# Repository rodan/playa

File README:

This project has the following feature set:

   - a smallish and spartan music player that can work for weeks between charges
   - a 2Ah Li-poly cell and an integrated charger - 5V input
   - decoding of ogg vorbis, mp3 files
   - microSD (SDHC) is the storage medium. so fat32 and cards bigger than 4G.

  there are 2 components in this repository:
  avr        - contains the C source code for an Atmel-based microcontroller
  beaglebone - contains the C source code for beagle-bone (ARMv7)-based tools
  hardware   - open source hardware for the main board
				the schematic is based on VLSI's Simple DSP Evaluation Board [1]

  Library dependencies for the avr code:

   if using the master branch:
      none (this is a fully standalone version)

   if using the old 'arduino' branch:
      sdfatlib    http://code.google.com/p/sdfatlib/
      vs1063      https://github.com/rodan/vs1063
      IRremote    https://github.com/shirriff/Arduino-IRremote

  Usage:
   - an RC5 remote control provides the control (a Vishay TSOP IR receiver's output goes to PD2).
   - by default music files are played randomly. the following buttons are configured:
   
    VOL-        decrease volume
    VOL+        increase volume
    SUBTITLES   switch between 4 levels of spatial processing (for headphones)
    REWIND      switch to album mode
    CHANNEL-    switch to artist mode
    CHANNEL+    next track in either of the modes
    STOP        sends the player in low power shutdown mode. 
                you need to start it again to exit this.
    NUMBERS 0-9 select artist (which directory from the root of the filesystem to play)
    AV          disable artist selection

  Power consumption profile:
   - jumper/switch open - battery connected only to the charging circuit - < 3uA
   - normal file decoding - 30-40 mA
   - shutdown (after STOP ir command), IR sensor active - 800uA
   - after uC woken up by ir sensor trigger, waiting for a POWER ir sequence (for max 2 seconds) - 4.5mA (this mode has been disabled in the code)
   - if the stereo jack is unused or if the battery level goes below safe LiPo levels then the player enters shutdown mode.

  Known problems and limitations:
   - you should format the SDcard as Fat32 with largest available cluster size
   - no special chars must be used in the filesystem entries, only ascii alphanumeric chars
   - there is a hardcoded MAX_PATH that only allows about 4 parent dirs to any music file

  Tested with:
   - 16G Class 10 Adata card, with ogg files over the 4G barrier

  Author:            Petre Rodan <2b4eda@subdimension.ro>
  Available from:    https://github.com/rodan/playa
  Product pictures:  https://photos.app.goo.gl/nUQuD7HJvfVBpMeQ9
  License:           GNU GPLv3

[1]  http://www.vlsi.fi/en/support/evaluationboards/vs1053vs8053simpledspboard.html

 GNU GPLv3 license:
  
  This program is free software: you can redistribute it and/or modify
  it under the terms of the GNU General Public License as published by
  the Free Software Foundation, either version 3 of the License, or
  (at your option) any later version.
   
  This program is distributed in the hope that it will be useful,
  but WITHOUT ANY WARRANTY; without even the implied warranty of
  MERCHANTABILITY or FITNESS FOR A PARTICULAR PURPOSE.  See the
  GNU General Public License for more details.
   
  You should have received a copy of the GNU General Public License
  along with this program.  If not, see <http://www.gnu.org/licenses/>.

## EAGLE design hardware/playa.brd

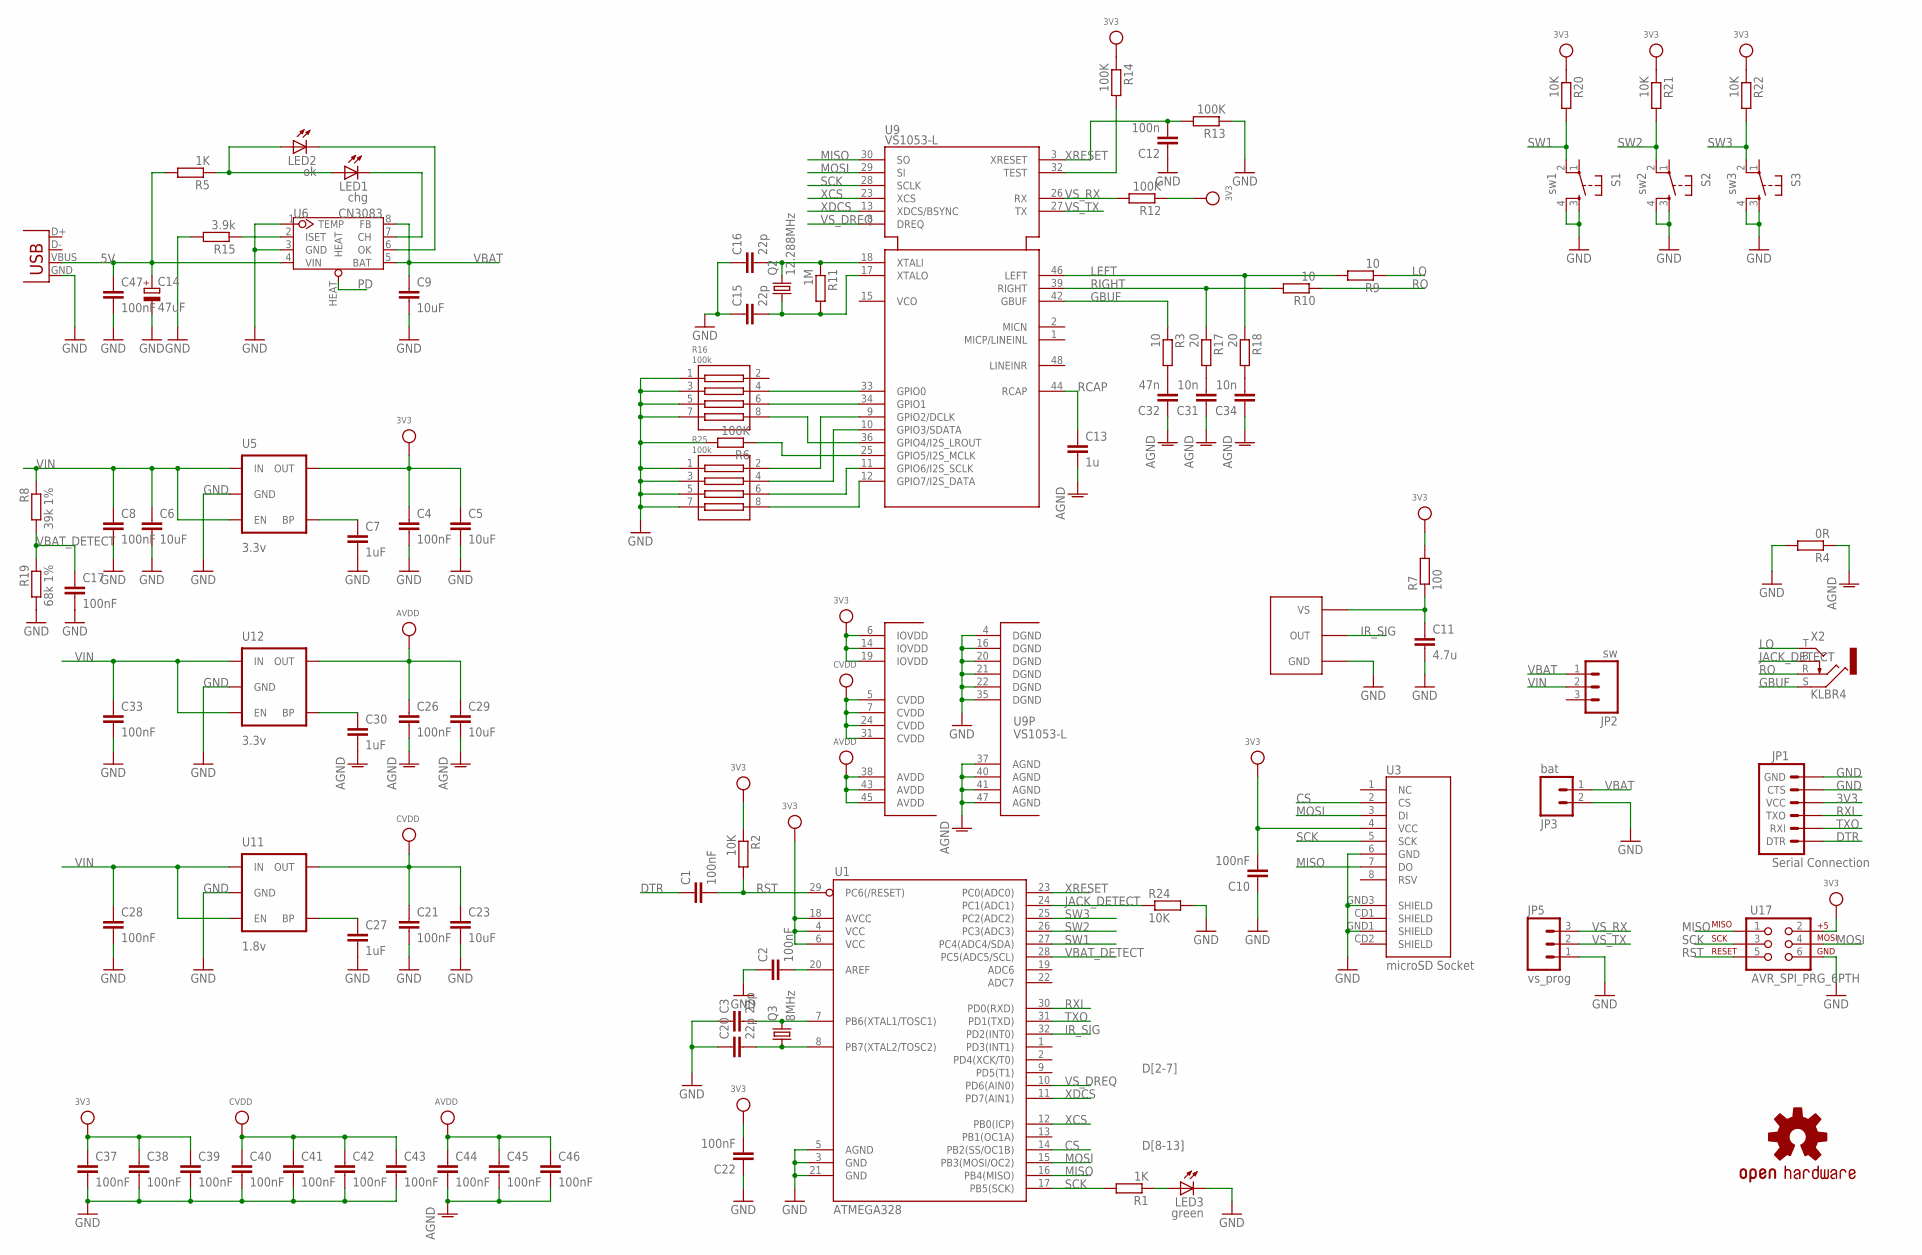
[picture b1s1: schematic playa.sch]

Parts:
C1, C2, C4, C8, C10, C17, C21, C22, C26, C28, C33, C37, C38, C39, C40, C41, C42, C43, C44, C45, C46, C47: 100nF; C0805
C3, C15, C16, C20: 22p; C0805
C5, C6, C9, C23, C29: 10uF; C1206
C7, C27, C30: 1uF; C0805
C11: 4.7u; C1206
C12: 100n; C0805
C13: 1u; C0805
C14: 47uF; CT7343
C31, C34: 10n; C0805
C32: 47n; C0805
JP1: Serial Connection; 1X06
JP2: sw; 1X03
JP3: bat; 1X02
JP5: vs_prog; 1X03
LED1: chg; CHIP-LED0805
LED2: ok; CHIP-LED0805
LED3: green; CHIP-LED0805
Q2: 12.288MHz; CRYSTAL_5X3.2
Q3: 8MHz; CRYSTAL_5X3.2
R1, R5: 1K; R0805W
R2, R20, R21, R22, R24: 10K; R0805W
R3, R9, R10: 10; R0805W
R4: 0R; R0805W
R6, R12, R13, R14: 100K; R0805W
R7: 100; R0805W
R8: 39k 1%; R0805W
R11: 1M; R0805W
R15: 3.9k; R0805W
R16, R25: 100k; RAS_ARR_1206
R17, R18: 20; R0805W
R19: 68k 1%; R0805W
S1: sw1; TACTILE_SWITCH_SMD
S2: sw2; TACTILE_SWITCH_SMD
S3: sw3; TACTILE_SWITCH_SMD
U1: ATMEGA328; TQFP32-08
U3: microSD Socket; MICRO-SD-SOCKET-PP
U5, U12: 3.3v; SOT23-5
U6: CN3083; SOP8-W/-HEAT
U9: VS1053-L; LQFP48
U11: 1.8v; SOT23-5
U17: AVR_SPI_PRG_6PTH; 2X3
U$3: TSOP312X
U$5: OSHW-LOGOM; OSHW-LOGO-M
X1: USBSMD; USB-MINIB
X2: KLBR4

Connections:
3V3: C4.1, C5.1, C10.2, C22.2, C37.1, C38.1, C39.1, JP1.4 (VCC), R2.1, R7.2, R12.1, R14.1, R20.1, R21.1, R22.1, U1.4 (VCC), U1.6 (VCC), U1.18 (AVCC), U3.4 (VCC), U5.5 (OUT), U9.6 (IOVDD), U9.14 (IOVDD), U9.19 (IOVDD), U17.2
5V: C14.+, C47.1, R5.2, U6.4 (VIN), X1.VBUS
AGND: C13.2, C26.2, C29.2, C30.2, C31.1, C32.1, C34.1, C44.2, C45.2, C46.2, R4.1, U9.37 (AGND), U9.40 (AGND), U9.41 (AGND), U9.47 (AGND)
AVDD: C26.1, C29.1, C44.1, C45.1, C46.1, U9.38 (AVDD), U9.43 (AVDD), U9.45 (AVDD), U12.5 (OUT)
CS: U1.14 (PB2(SS/OC1B)), U3.2 (CS)
CVDD: C21.1, C23.1, C40.1, C41.1, C42.1, C43.1, U9.5 (CVDD), U9.7 (CVDD), U9.24 (CVDD), U9.31 (CVDD), U11.5 (OUT)
DTR: C1.1, JP1.1 (DTR)
GBUF: R3.1, U9.42 (GBUF), X2.S
GND: C2.1, C3.1, C4.2, C5.2, C6.2, C7.2, C8.2, C9.2, C10.1, C11.2, C12.1, C14.-, C15.1, C16.1, C17.2, C20.1, C21.2, C22.1, C23.2, C27.2, C28.2, C33.2, C37.2, C38.2, C39.2, C40.2, C41.2, C42.2, C43.2, C47.2, JP1.5 (CTS), JP1.6 (GND), JP3.2, JP5.1, LED3.C, R4.2, R6.2, R13.1, R15.2, R16.1, R16.3, R16.5, R16.7, R19.2, R24.2, R25.1, R25.3, R25.5, R25.7, S1.3, S1.4, S2.3, S2.4, S3.3, S3.4, U1.3 (GND), U1.5 (AGND), U1.21 (GND), U3.6 (GND), U3.GND1 (SHIELD), U3.GND3 (SHIELD), U5.2 (GND), U6.1 (TEMP), U6.3 (GND), U9.4 (DGND), U9.16 (DGND), U9.20 (DGND), U9.21 (DGND), U9.22 (DGND), U9.35 (DGND), U11.2 (GND), U12.2 (GND), U17.6, U$3.1 (GND), X1.GND
IR_SIG: U1.32 (PD2(INT0)), U$3.3 (OUT)
JACK_DETECT: R24.1, U1.24 (PC1(ADC1)), X2.B
LEFT: R9.2, R18.1, U9.46 (LEFT)
LO: R9.1, X2.T
MISO: U1.16 (PB4(MISO)), U3.7 (DO), U9.30 (SO), U17.1
MOSI: U1.15 (PB3(MOSI/OC2)), U3.3 (DI), U9.29 (SI), U17.4
unnamed: C20.2, Q3.P$1 (1), U1.8 (PB7(XTAL2/TOSC2))
unnamed: C3.2, Q3.P$2 (2), U1.7 (PB6(XTAL1/TOSC1))
unnamed: C2.2, U1.20 (AREF)
unnamed: R16.4, U9.33 (GPIO0)
unnamed: C7.1, U5.4 (BP)
unnamed: R25.8, U9.12 (GPIO7/I2S_DATA)
unnamed: C27.1, U11.4 (BP)
unnamed: C32.2, R3.2
unnamed: R15.1, U6.2 (ISET)
unnamed: C31.2, R17.2
unnamed: C34.2, R18.2
unnamed: R16.6, U9.34 (GPIO1)
unnamed: LED3.A, R1.1
unnamed: LED1.A, LED2.A, R5.1
unnamed: LED1.C, U6.7 (CH)
unnamed: LED2.C, U6.6 (OK)
unnamed: R16.8, U9.36 (GPIO4/I2S_LROUT)
unnamed: C30.1, U12.4 (BP)
unnamed: R6.1, U9.25 (GPIO5/I2S_MCLK)
unnamed: R25.2, U9.9 (GPIO2/DCLK)
unnamed: R25.4, U9.10 (GPIO3/SDATA)
unnamed: R25.6, U9.11 (GPIO6/I2S_SCLK)
unnamed: C11.1, R7.1, U$3.2 (VS)
unnamed: R14.2, U9.32 (TEST)
PD: U6.HEAT
RCAP: C13.1, U9.44 (RCAP)
RIGHT: R10.2, R17.1, U9.39 (RIGHT)
RO: R10.1, X2.R
RST: C1.2, R2.2, U1.29 (PC6(/RESET)), U17.5
RXI: JP1.3 (TXO), U1.30 (PD0(RXD))
SCK: R1.2, U1.17 (PB5(SCK)), U3.5 (SCK), U9.28 (SCLK), U17.3
SW1: R20.2, S1.2, U1.27 (PC4(ADC4/SDA))
SW2: R21.2, S2.2, U1.26 (PC3(ADC3))
SW3: R22.2, S3.2, U1.25 (PC2(ADC2))
TXO: JP1.2 (RXI), U1.31 (PD1(TXD))
VBAT: C9.1, JP2.1, JP3.1, U6.5 (BAT), U6.8 (FB)
VBAT_DETECT: C17.1, R8.2, R19.1, U1.28 (PC5(ADC5/SCL))
VIN: C6.1, C8.1, C28.1, C33.1, JP2.2, R8.1, U5.1 (IN), U5.3 (EN), U11.1 (IN), U11.3 (EN), U12.1 (IN), U12.3 (EN)
VS_DREQ: U1.10 (PD6(AIN0)), U9.8 (DREQ)
VS_RX: JP5.3, R12.2, U9.26 (RX)
VS_TX: JP5.2, U9.27 (TX)
VS_XTALI: C16.2, Q2.P$2 (2), R11.1, U9.18 (XTALI)
VS_XTALO: C15.2, Q2.P$1 (1), R11.2, U9.17 (XTALO)
XCS: U1.12 (PB0(ICP)), U9.23 (XCS)
XDCS: U1.11 (PD7(AIN1)), U9.13 (XDCS/BSYNC)
XRESET: C12.2, R13.2, U1.23 (PC0(ADC0)), U9.3 (XRESET)

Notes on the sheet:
D[2-7]
D[8-13]

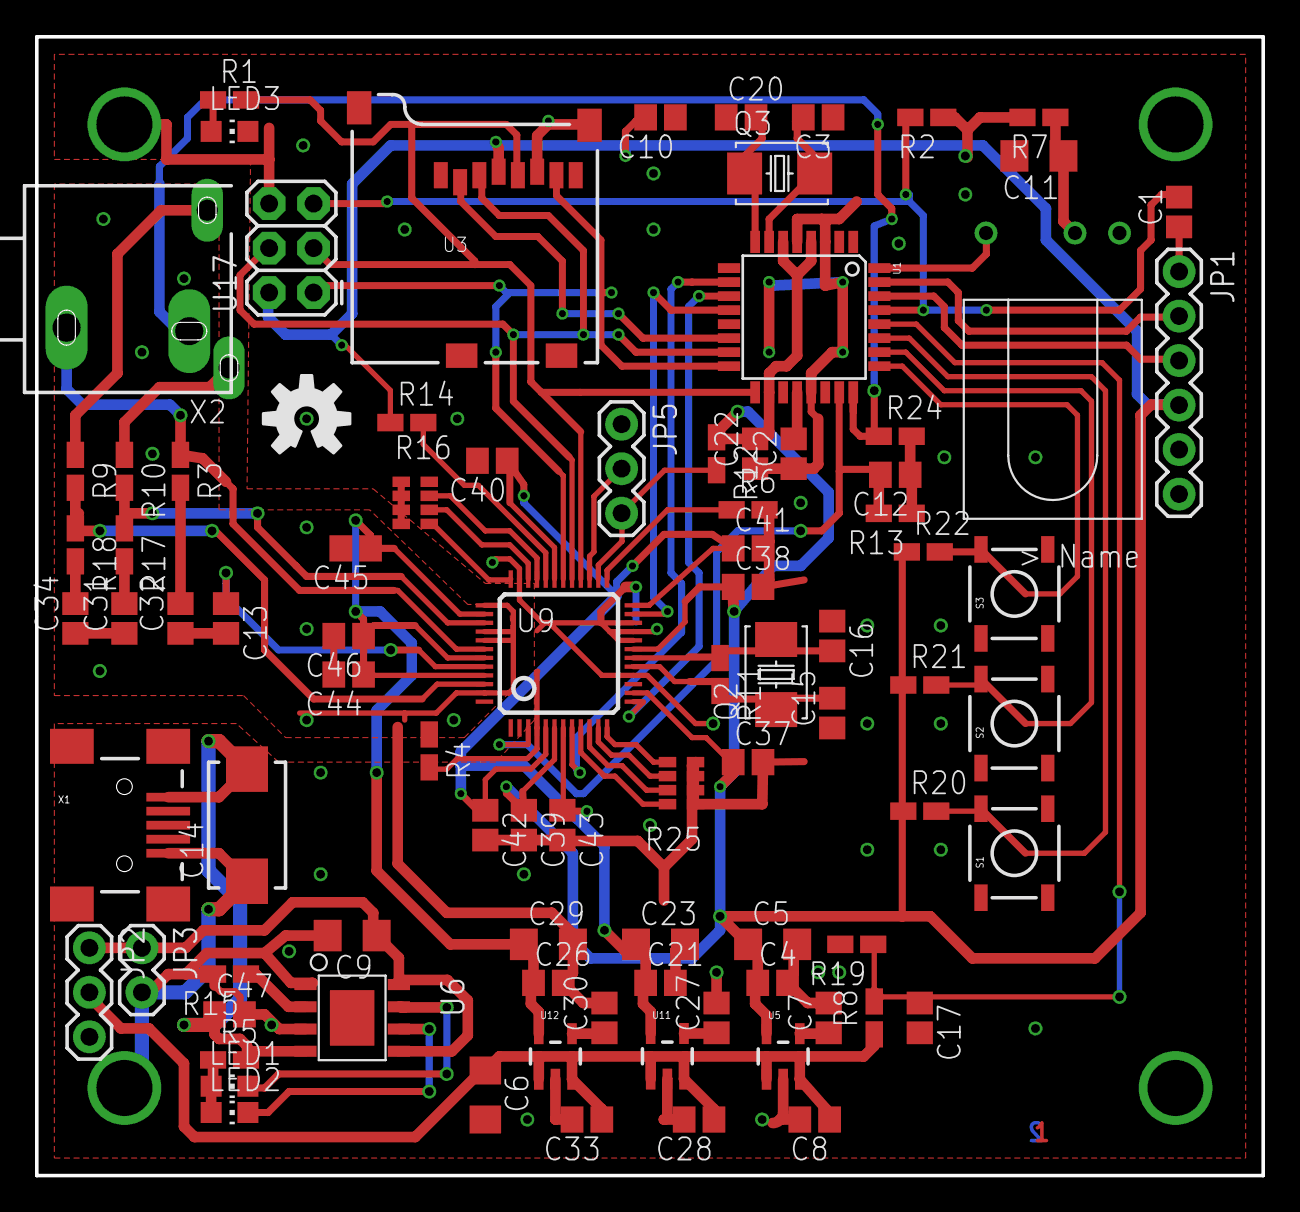
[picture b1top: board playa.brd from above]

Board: 2 copper layers, 70.0 x 65.0 mm, 89 parts (0 on the bottom side), 60 nets.

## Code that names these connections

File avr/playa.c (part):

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    //   in case the cell voltage is below ~3.5v, vbat is not read correctly
    //   and the only thing protecting the cell is the internal cutoff

    vbat = analogRead(PIN_VBAT_DETECT);
    jack_detect = analogRead(PIN_JACK_DETECT);

    // attempt to gather some entropy from the outside
    // sometimes PIN_RANDOM gives the same values, so keep and increment seed between runs
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        vs_select_data();
        i = 0;
        while (i < r) {
            while (!(VS_DREQ_PIN & VS_DREQ)) {
                // the VS chip is busy, so do something else
                vs_deselect_data();     // Release the SDI bus
                wdt_reset();
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
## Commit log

2012-01-21 makefile added
2012-01-21 sch update
2012-01-21 add known limitations to the README
2012-01-22 get closer to the datasheet
2012-01-22 do codec checks and implement ogg replaygain volume
2012-01-22 replaygain tweaks
2012-01-25 pcb completed
2012-01-27 play random files in the nth directory of root, using the numbers on the remote
2012-02-01 added TSOP31236 pkg and voltage sensing
2012-02-04 latest pcb
2012-02-05 sent to manufacture
2012-02-14 use unconnected pin for random seed
2012-03-06 link to the final product pictures
2012-03-06 fixed vbat voltage sensing resistor values
2012-03-18 detect battery voltage and stereo jack status
2012-03-18 modify battery voltage divider. it currently uses 35uA
2012-06-29 verify accu charge, add sony rc decode values
2012-09-13 looks like randomseed is broken
2012-10-13 move pde to ino
2012-11-17 watchdog and sleep mode
2012-11-17 indent
2012-11-17 only allow 'power' IR sequence to wake up uC
2012-11-17 cleanup
2012-11-17 cleanup part2
2012-11-18 enter the STOP loop only once
2012-11-18 add power consumption profile
2013-05-25 add v2 branch
2013-05-25 add reference to v2 into README
2013-05-25 add ir_remote driver
2013-05-25 sdcard f_open working
2013-05-25 fix indent
2013-05-25 ir_decode is working
2013-05-25 sound!
2013-05-25 ui added
2013-05-25 use FS_TINY
2013-05-26 working v2
2013-05-26 adc is working
2013-05-26 SLEEP_MODE_PWR_DOWN kinda working
2013-05-26 add vs_fill
2013-05-26 tweak spi_transmit_sync
2013-05-26 end decoding properly
2013-05-27 rename traces to match the names given in the source code
2013-05-27 compilation warnings fixed
2013-05-27 no more waking up
2013-05-27 add interface for the ear speaker spatial processing
2013-05-27 cleanup the README
2013-05-27 enable MISO pull-ul in software
2018-09-01 email change
2019-03-03 add beaglebone OS setup files
2019-03-03 add devmem handling
2019-03-05 latest
2019-03-08 spi0 - latest
2019-03-08 switch to SPI1
2019-03-08 SPI1 latest
2019-06-20 epoll inside DREQ irq handling
2019-06-20 gpio is exported at runtime
2019-06-21 add 230b patches
2019-06-22 new init
2019-06-22 fix stream play canceling
2019-06-23 fix flac file closing with 0x800 SCI_MODE after cancel
